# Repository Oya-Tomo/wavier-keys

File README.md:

# Wavier Keys Firmware and Circuit

## tech

## description

this repo contains the firmware program written in Rust with rp-2040 bsp and circuit file made with kicad.

test, test, ah... ah...
This message was written with Wavier Keys keyboard.

## author

Oya-Tomo

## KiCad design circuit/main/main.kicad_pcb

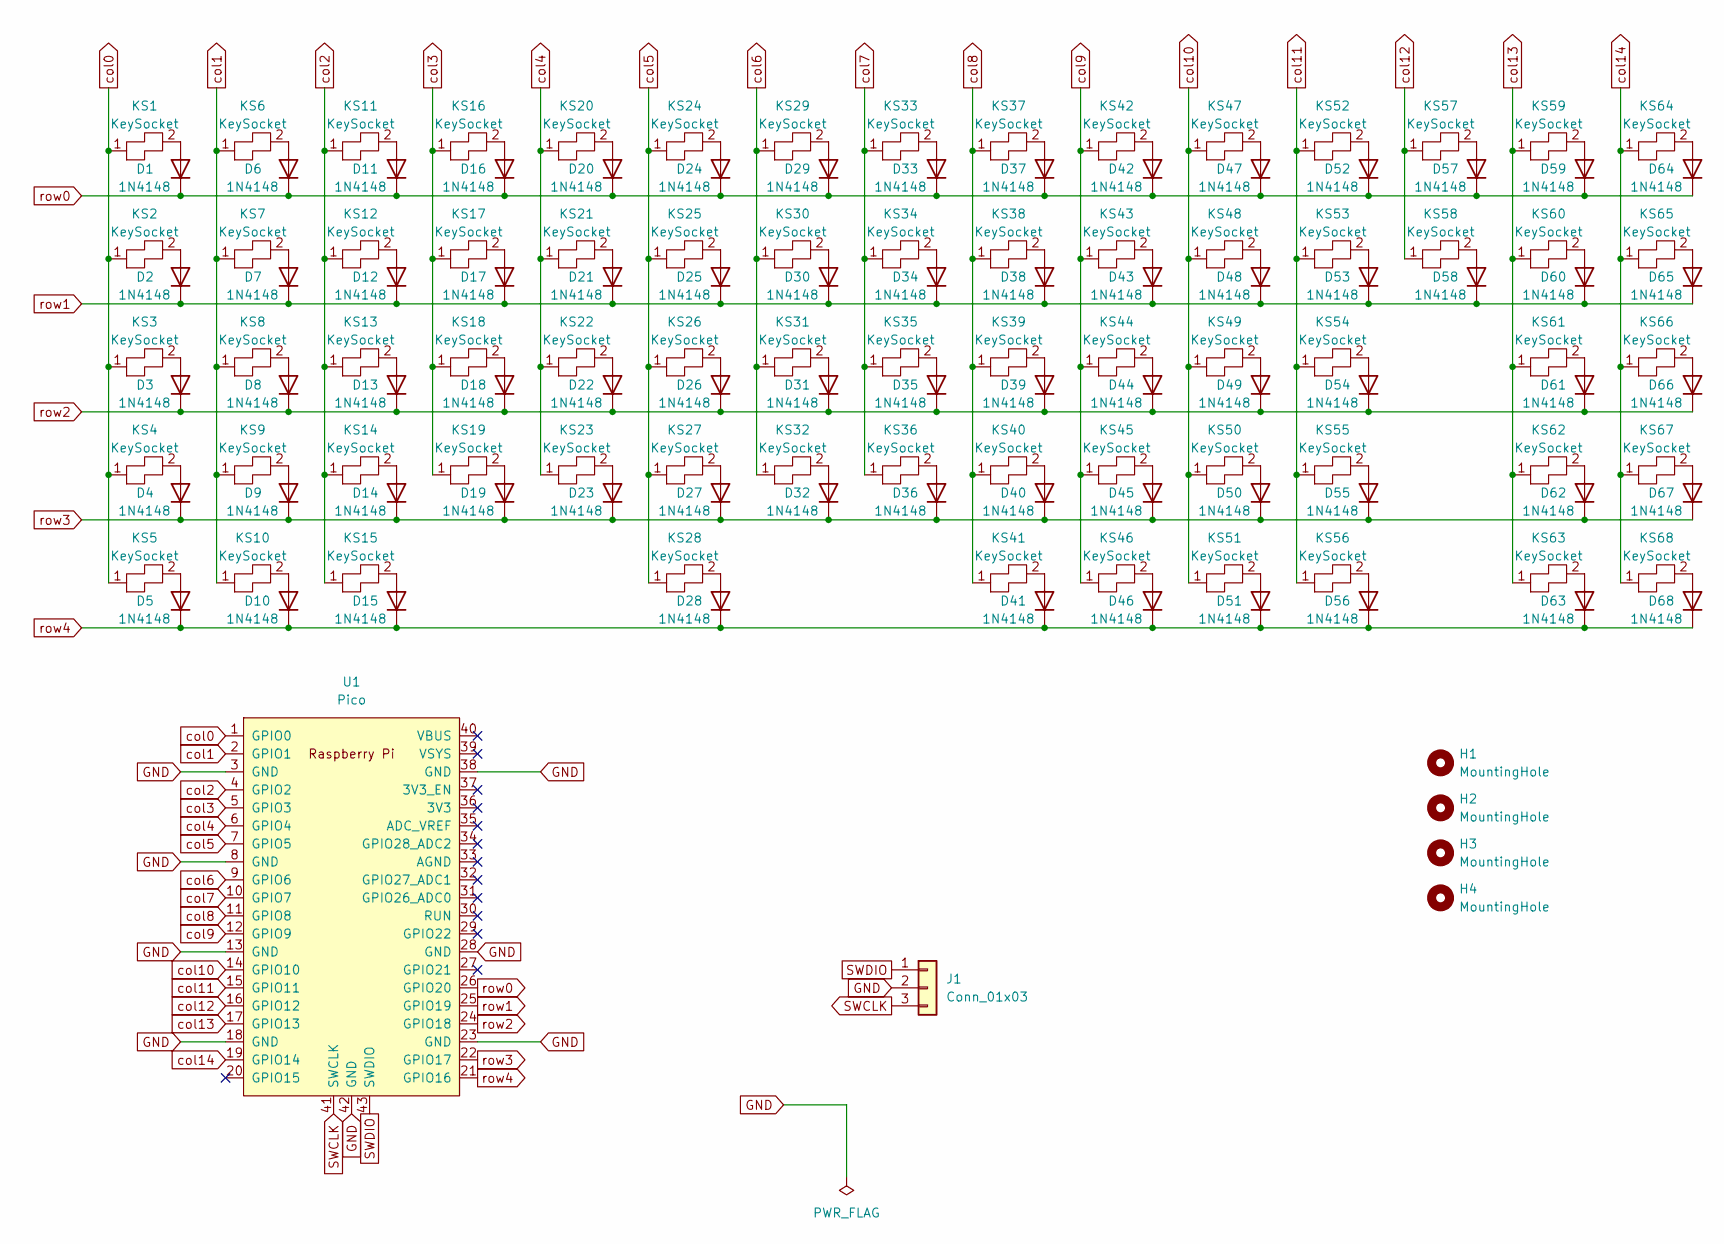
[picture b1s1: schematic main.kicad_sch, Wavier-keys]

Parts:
D1, D2, D3, D4, D5, D6, D7, D8, D9, D10, D11, D12, D13, D14, D15, D16, D17, D18, D19, D20, D21, D22, D23, D24, D25, D26, D27, D28, D29, D30, D31, D32, D33, D34, D35, D36, D37, D38, D39, D40, D41, D42, D43, D44, D45, D46, D47, D48, D49, D50, D51, D52, D53, D54, D55, D56, D57, D58, D59, D60, D61, D62, D63, D64, D65, D66, D67, D68: 1N4148; D_DO-35_SOD27_P7.62mm_Horizontal
H1, H2, H3, H4: MountingHole; MountingHole_2.5mm
J1: Conn_01x03; PinHeader_1x03_P2.54mm_Horizontal
KS1, KS6, KS7, KS8, KS9, KS11, KS12, KS13, KS14, KS16, KS17, KS18, KS19, KS20, KS21, KS22, KS23, KS24, KS25, KS26, KS27, KS29, KS30, KS31, KS32, KS33, KS34, KS35, KS36, KS37, KS38, KS39, KS40, KS41, KS42, KS43, KS44, KS45, KS46, KS47, KS48, KS49, KS50, KS51, KS52, KS53, KS54, KS56, KS57, KS58, KS59, KS62, KS63, KS65, KS66, KS67, KS68: KeySocket; SW_Hotswap_Kailh_MX_1.00u
KS2, KS60: KeySocket; SW_Hotswap_Kailh_MX_1.50u
KS3, KS55: KeySocket; SW_Hotswap_Kailh_MX_1.75u
KS4, KS61: KeySocket; SW_Hotswap_Kailh_MX_2.25u
KS5, KS10, KS15: KeySocket; SW_Hotswap_Kailh_MX_1.25u
KS28: KeySocket; SW_Hotswap_Kailh_MX_6.25u
KS64: KeySocket; SW_Hotswap_Kailh_MX_2.00u
U1: Pico; RPi_Pico_SMD_TH

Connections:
GND: J1.2, U1.3 (GND), U1.8 (GND), U1.13 (GND), U1.18 (GND), U1.23 (GND), U1.28 (GND), U1.38 (GND), U1.42 (GND)
unnamed: D1.2 (A), KS1.2
unnamed: D2.2 (A), KS2.2
unnamed: D3.2 (A), KS3.2
unnamed: D4.2 (A), KS4.2
unnamed: D5.2 (A), KS5.2
unnamed: D6.2 (A), KS6.2
unnamed: D7.2 (A), KS7.2
unnamed: D8.2 (A), KS8.2
unnamed: D9.2 (A), KS9.2
unnamed: D10.2 (A), KS10.2
unnamed: D11.2 (A), KS11.2
unnamed: D12.2 (A), KS12.2
unnamed: D13.2 (A), KS13.2
unnamed: D14.2 (A), KS14.2
unnamed: D15.2 (A), KS15.2
unnamed: D16.2 (A), KS16.2
unnamed: D17.2 (A), KS17.2
unnamed: D18.2 (A), KS18.2
unnamed: D19.2 (A), KS19.2
unnamed: D20.2 (A), KS20.2
unnamed: D21.2 (A), KS21.2
unnamed: D22.2 (A), KS22.2
unnamed: D23.2 (A), KS23.2
unnamed: D24.2 (A), KS24.2
unnamed: D25.2 (A), KS25.2
unnamed: D26.2 (A), KS26.2
unnamed: D27.2 (A), KS27.2
unnamed: D28.2 (A), KS28.2
unnamed: D29.2 (A), KS29.2
unnamed: D30.2 (A), KS30.2
unnamed: D31.2 (A), KS31.2
unnamed: D32.2 (A), KS32.2
unnamed: D33.2 (A), KS33.2
unnamed: D34.2 (A), KS34.2
unnamed: D35.2 (A), KS35.2
unnamed: D36.2 (A), KS36.2
unnamed: D37.2 (A), KS37.2
unnamed: D38.2 (A), KS38.2
unnamed: D39.2 (A), KS39.2
unnamed 40: D40.2 (A), KS40.2; also elsewhere on the board
unnamed: D41.2 (A), KS41.2
unnamed 42: D42.2 (A), KS42.2; also elsewhere on the board
unnamed: D43.2 (A), KS43.2
unnamed: D44.2 (A), KS44.2
unnamed: D45.2 (A), KS45.2
unnamed: D46.2 (A), KS46.2
unnamed: D47.2 (A), KS47.2
unnamed: D48.2 (A), KS48.2
unnamed: D49.2 (A), KS49.2
unnamed: D50.2 (A), KS50.2
unnamed: D51.2 (A), KS51.2
unnamed: D52.2 (A), KS52.2
unnamed: D53.2 (A), KS53.2
unnamed: D54.2 (A), KS54.2
unnamed: D55.2 (A), KS55.2
unnamed: D56.2 (A), KS56.2
unnamed: D57.2 (A), KS57.2
unnamed: D58.2 (A), KS58.2
unnamed: D59.2 (A), KS59.2
unnamed: D60.2 (A), KS60.2
unnamed: D61.2 (A), KS61.2
unnamed: D62.2 (A), KS62.2
unnamed: D63.2 (A), KS63.2
unnamed: D64.2 (A), KS64.2
unnamed: D65.2 (A), KS65.2
unnamed: D66.2 (A), KS66.2
unnamed: D67.2 (A), KS67.2
unnamed: D68.2 (A), KS68.2
SWCLK: J1.3, U1.41 (SWCLK)
SWDIO: J1.1, U1.43 (SWDIO)
col0: KS1.1, KS2.1, KS3.1, KS4.1, KS5.1, U1.1 (GPIO0)
col1: KS6.1, KS7.1, KS8.1, KS9.1, KS10.1, U1.2 (GPIO1)
col2: KS11.1, KS12.1, KS13.1, KS14.1, KS15.1, U1.4 (GPIO2)
col3: KS16.1, KS17.1, KS18.1, KS19.1, U1.5 (GPIO3)
col4: KS20.1, KS21.1, KS22.1, KS23.1, U1.6 (GPIO4)
col5: KS24.1, KS25.1, KS26.1, KS27.1, KS28.1, U1.7 (GPIO5)
col6: KS29.1, KS30.1, KS31.1, KS32.1, U1.9 (GPIO6)
col7: KS33.1, KS34.1, KS35.1, KS36.1, U1.10 (GPIO7)
col8: KS37.1, KS38.1, KS39.1, KS40.1, KS41.1, U1.11 (GPIO8); also elsewhere on the board
col9: KS42.1, KS43.1, KS44.1, KS45.1, KS46.1, U1.12 (GPIO9); also elsewhere on the board
col10: KS47.1, KS48.1, KS49.1, KS50.1, KS51.1, U1.14 (GPIO10)
col11: KS52.1, KS53.1, KS54.1, KS55.1, KS56.1, U1.15 (GPIO11)
col12: KS57.1, KS58.1, U1.16 (GPIO12)
col13: KS59.1, KS60.1, KS61.1, KS62.1, KS63.1, U1.17 (GPIO13)
col14: KS64.1, KS65.1, KS66.1, KS67.1, KS68.1, U1.19 (GPIO14)
row0: D1.1 (K), D6.1 (K), D11.1 (K), D16.1 (K), D20.1 (K), D24.1 (K), D29.1 (K), D33.1 (K), D37.1 (K), D42.1 (K), D47.1 (K), D52.1 (K), D57.1 (K), D59.1 (K), D64.1 (K), U1.26 (GPIO20)
row1: D2.1 (K), D7.1 (K), D12.1 (K), D17.1 (K), D21.1 (K), D25.1 (K), D30.1 (K), D34.1 (K), D38.1 (K), D43.1 (K), D48.1 (K), D53.1 (K), D58.1 (K), D60.1 (K), D65.1 (K), U1.25 (GPIO19)
row2: D3.1 (K), D8.1 (K), D13.1 (K), D18.1 (K), D22.1 (K), D26.1 (K), D31.1 (K), D35.1 (K), D39.1 (K), D44.1 (K), D49.1 (K), D54.1 (K), D61.1 (K), D66.1 (K), U1.24 (GPIO18)
row3: D4.1 (K), D9.1 (K), D14.1 (K), D19.1 (K), D23.1 (K), D27.1 (K), D32.1 (K), D36.1 (K), D40.1 (K), D45.1 (K), D50.1 (K), D55.1 (K), D62.1 (K), D67.1 (K), U1.22 (GPIO17)
row4: D5.1 (K), D10.1 (K), D15.1 (K), D28.1 (K), D41.1 (K), D46.1 (K), D51.1 (K), D56.1 (K), D63.1 (K), D68.1 (K), U1.21 (GPIO16)

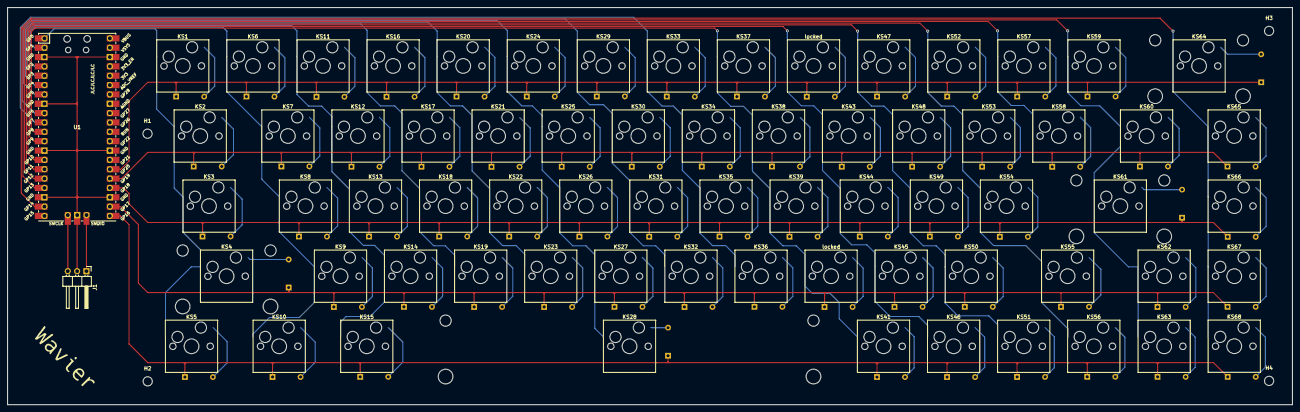
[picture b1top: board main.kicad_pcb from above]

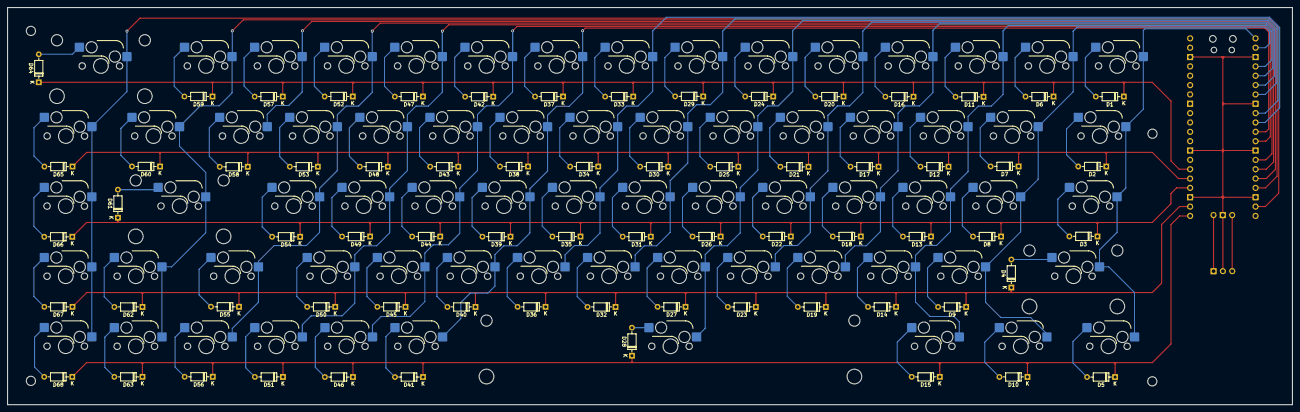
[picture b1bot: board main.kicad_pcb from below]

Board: 2 copper layers, 349.2 x 108.0 mm, 142 parts (68 on the bottom side), 91 nets.

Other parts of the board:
locked: KeySocket; SW_Hotswap_Kailh_MX_1.00u
locked#2: locked; SW_Hotswap_Kailh_MX_1.00u

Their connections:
unnamed 40: locked#2.2; also elsewhere on the board
unnamed 42: locked.2; also elsewhere on the board
col8: locked#2.1; also elsewhere on the board
col9: locked.1; also elsewhere on the board

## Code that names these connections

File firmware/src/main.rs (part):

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    let sio = rp_pico::hal::Sio::new(dp.SIO);
    let pins = rp_pico::Pins::new(dp.IO_BANK0, dp.PADS_BANK0, sio.gpio_bank0, &mut dp.RESETS);

    let col0 = pins.gpio0.into_pull_up_input();
    let col1 = pins.gpio1.into_pull_up_input();
    let col2 = pins.gpio2.into_pull_up_input();
    let col3 = pins.gpio3.into_pull_up_input();
    let col4 = pins.gpio4.into_pull_up_input();
    let col5 = pins.gpio5.into_pull_up_input();
    let col6 = pins.gpio6.into_pull_up_input();
    let col7 = pins.gpio7.into_pull_up_input();
    let col8 = pins.gpio8.into_pull_up_input();
    let col9 = pins.gpio9.into_pull_up_input();
    let col10 = pins.gpio10.into_pull_up_input();
    let col11 = pins.gpio11.into_pull_up_input();
    let col12 = pins.gpio12.into_pull_up_input();
    let col13 = pins.gpio13.into_pull_up_input();
    let col14 = pins.gpio14.into_pull_up_input();

    let mut row0 = pins.gpio20.into_push_pull_output();
    let mut row1 = pins.gpio19.into_push_pull_output();
    let mut row2 = pins.gpio18.into_push_pull_output();
    let mut row3 = pins.gpio17.into_push_pull_output();
    let mut row4 = pins.gpio16.into_push_pull_output();

    let mut led = pins.led.into_push_pull_output();

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
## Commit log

2023-09-01 first commit & completed
2023-09-01 docs: added description in README.md
2023-09-04 update: added idling stop feature -beta
2023-09-13 update: added mouse feature -beta
2023-09-18 fixed: frame rate && saving feature -beta
